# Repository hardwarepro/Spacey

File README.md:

# Spacey
A fully open-source space mouse! The current space mouse costs around $350 USD, so being able to build it for ~$75 USD is a HUGE reduction is cost for the same features (minus the screen). It has 10 hotkeyabled buttons, LEDs, a magnetometor for the space mouse part of it, and an amazingly designed CAD!

There are 2 main parts to this space mouse, the CAD + PCB for the keyboard, and the few parts for the space mouse part of it. Some photos of the CAD can be seen below, and can be viewed [here](https://cad.onshape.com/documents/f05fe75dfc18f89f5fcec945/w/6a3c1056693be4c34d9f2601/e/94b3cceea32ed90fe954c1a2). The PCB controls all the hotkeys, and the Xiao + magnetometor controls the actual space mouse ascpect. The space mouse part was partially taken from a tutorial though this was fully expanded to support hotkeys to act like the real and production-wise space mouse. Since the tutorial only convered those few main parts, all of the PCB + CAD shown below was all designed by myself.

## Photos

## BOM

## Full Total: $77.47 USD

## Parts for the Keyboard Part of it
| Item                 | Description              | Quantity | Unit Price ($) | Total Price ($) | URL                                                                                                             | Running Total ($ with Tax) |
|----------------------|-------------------------|----------|----------------|----------------|-----------------------------------------------------------------------------------------------------------------|---------------------------|
| PCB                  | My PCB                  | x5       | $23.08         | $3.08          | [Link](https://jlcpcb.com)                                                                                      | $3.08                     |
| Case                 | 3D Printed              | 1        | Free           | Free           | N/A                                                                                                             | $0                        |
| XIAO-nRF52840        | MCU                     | 1        | $11.63         | $19.62         | [Link](https://ca.robotshop.com/fr/products/seeedstudioxiaonrf52840-fr?srsltid=AfmBOopHbke249HRHFvztYqPt2fS6K0UxMoKPbETLySdByMfJnvjifeVefc) | $19.62                     |
| Buttons + LEDs + Screw Terminal       | LCSC Parts for the PCB      | 15        | $20          | $20          | [Link](https://lcsc.com)                  | $20                       |
## Total with shipping + tax (USD): $42.7

## Parts for the space mouse part of it
| Item                 | Description              | Quantity | Unit Price ($) | Total Price ($) | URL                                                                                                             | Running Total ($ with Tax) |
|----------------------|-------------------------|----------|----------------|----------------|-----------------------------------------------------------------------------------------------------------------|---------------------------|
| Adafruit QT Py RP2040     | MCU                     | 1        | $9.95          | $9.95          | [Link](https://www.adafruit.com/product/4900) | N/A       |
| STEMMA QT / Qwiic JST SH 4-pin Cable - 50mm Long   | JST Cable | 1     | $0.95          | $0.95          | [Link][https://www.adafruit.com/product/4210](https://www.aliexpress.com/item/1005007590874378.html)                                            | N/A                     |
| Adafruit TLV493D      | The main chip for the mouse- the magnetometer                    | 1        | $5.71           | $7.70           | [Link][https://www.aliexpress.com/item/1005007590874378.html](https://www.adafruit.com/product/4366)                                                  | N/A                      |
| Magnets      | For the magnetometer                    | 1        | Free           | Free           | N/A                                                 | N/A                      |
## Total with shipping + tax (USD): $34.77

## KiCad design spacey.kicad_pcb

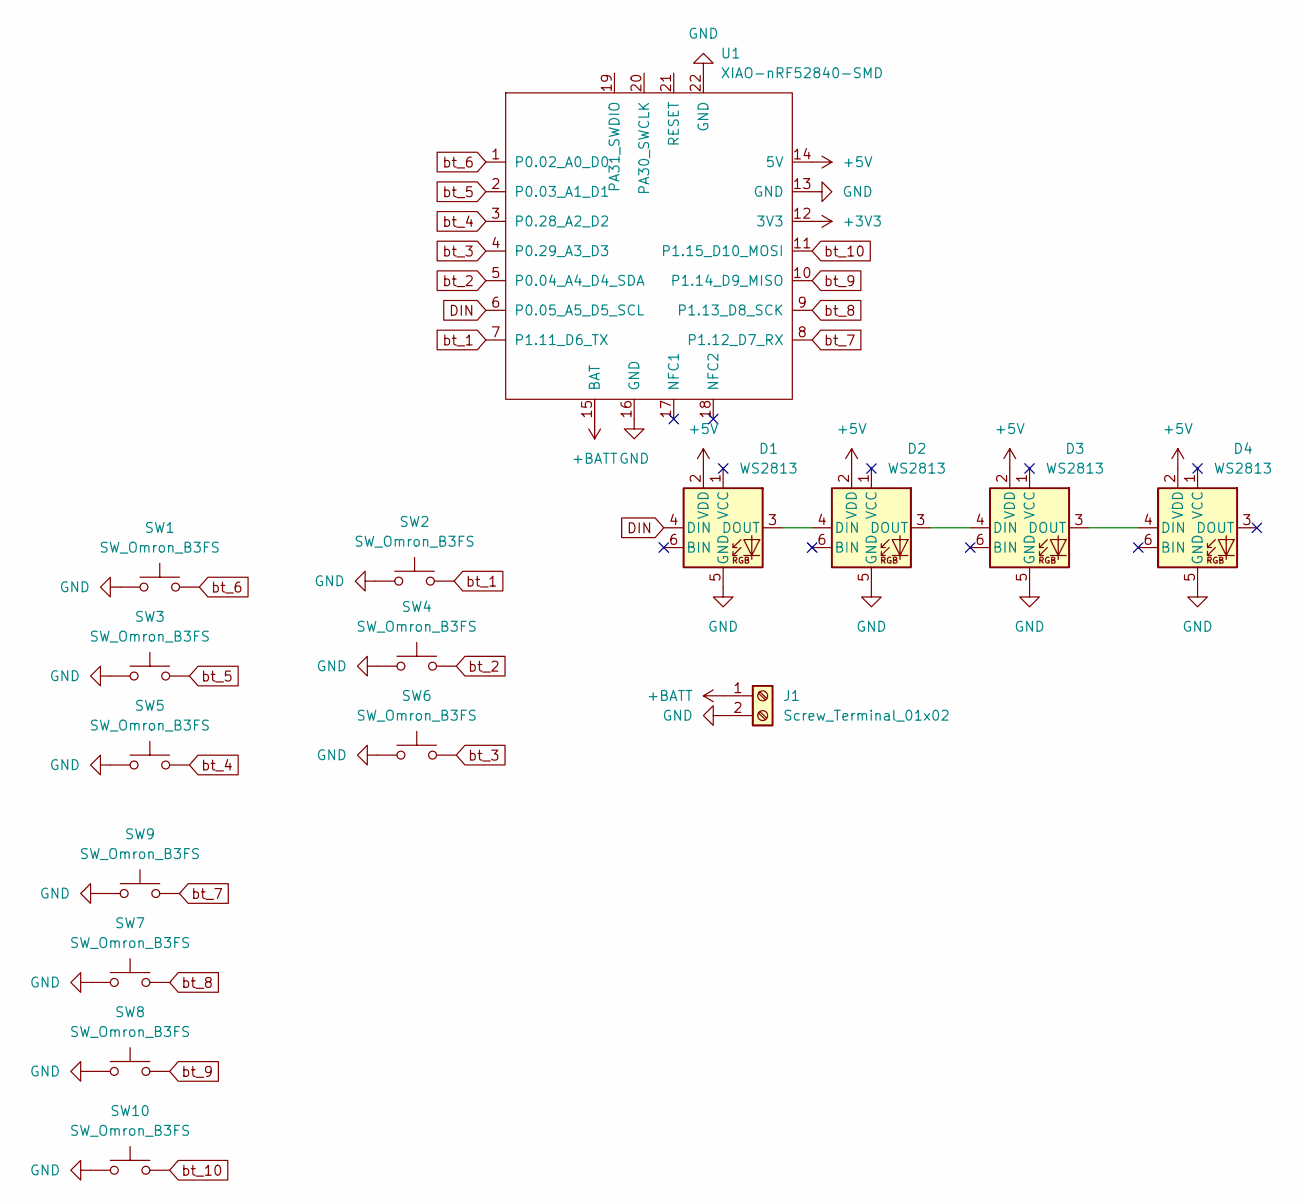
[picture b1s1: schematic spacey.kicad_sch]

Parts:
D1, D2, D3, D4: WS2813; LED_WS2812_PLCC6_5.0x5.0mm_P1.6mm
J1: Screw_Terminal_01x02; TerminalBlock_4Ucon_1x02_P3.50mm_Horizontal
SW1, SW2, SW3, SW4, SW5, SW6, SW7, SW8, SW9, SW10: SW_Omron_B3FS; SW_TH_Tactile_Omron_B3F-10xx
U1: XIAO-nRF52840-SMD

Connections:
+3V3: U1.12 (3V3)
+5V: D1.2 (VDD), D2.2 (VDD), D3.2 (VDD), D4.2 (VDD), U1.14 (5V)
+BATT: J1.1, U1.15 (BAT)
DIN: D1.4 (DIN), U1.6 (P0.05_A5_D5_SCL)
GND: D1.5 (GND), D2.5 (GND), D3.5 (GND), D4.5 (GND), J1.2, SW1.1, SW2.1, SW3.1, SW4.1, SW5.1, SW6.1, SW7.1, SW8.1, SW9.1, SW10.1, U1.13 (GND), U1.16 (GND), U1.22 (GND)
unnamed: D1.3 (DOUT), D2.4 (DIN)
unnamed: D2.3 (DOUT), D3.4 (DIN)
unnamed: D3.3 (DOUT), D4.4 (DIN)
bt_1: SW2.2, U1.7 (P1.11_D6_TX)
bt_2: SW4.2, U1.5 (P0.04_A4_D4_SDA)
bt_3: SW6.2, U1.4 (P0.29_A3_D3)
bt_4: SW5.2, U1.3 (P0.28_A2_D2)
bt_5: SW3.2, U1.2 (P0.03_A1_D1)
bt_6: SW1.2, U1.1 (P0.02_A0_D0)
bt_7: SW9.2, U1.8 (P1.12_D7_RX)
bt_8: SW7.2, U1.9 (P1.13_D8_SCK)
bt_9: SW8.2, U1.10 (P1.14_D9_MISO)
bt_10: SW10.2, U1.11 (P1.15_D10_MOSI)

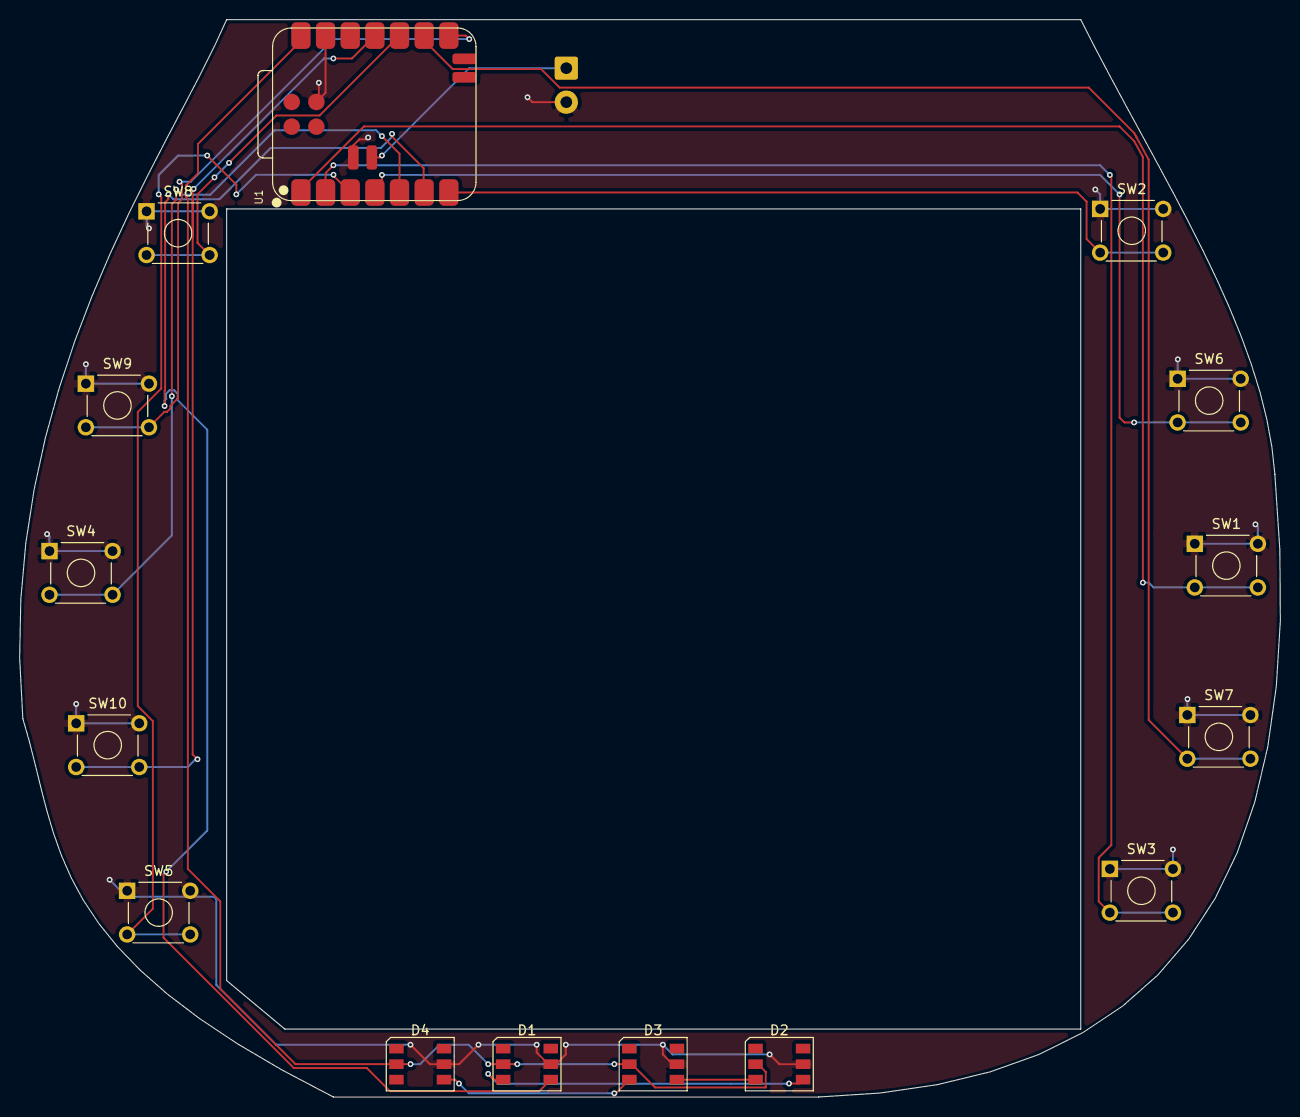
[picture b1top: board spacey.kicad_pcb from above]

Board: 2 copper layers, 129.9 x 111.0 mm, 16 parts (1 on the bottom side), 17 nets.

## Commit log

2025-12-04 Finished PCB
2025-12-12 Fixed DRC errors
2025-12-12 Added CAD and PCB folders
2025-12-12 Added JOURNAL.md
2025-12-12 Made the BOM.md
2025-12-12 Added my firmware
2025-12-12 Fixed README.md
2025-12-12 should be good now!
2025-12-12 added the 3d models + made a new step file
2025-12-13 Added new step file
    Update README.md
2025-12-14 Changed it to a .csv
2025-12-14 fixed?
